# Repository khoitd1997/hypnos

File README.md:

# hypnos

Module embedded inside users' laptop to "remind" them to take break and sleep

## Background

I used to have a script that runs every couple hours to turn the computer off to remind me to take a break. However, that script can be easily bypassed and it's not cross-platform. Embedding `hypnos` into the motherboard of my laptop and enabling tamperproof protection in the BIOS for the case make it much harder to bypass.

## Features

- Interact with device through phone app
  - Allow users' actions to be asynchronous, save and transmit their actions when the device is connected
  - Allow a limited number of exceptions through tokens per month: Allow users to select a time range that they don't want to be disturbed, the number of tokens needed are automatically calculated and applied
    - Waving sleep time as well as applying many tokens in the same day should cost more to prevent binge
  - Customizable work and break duration(there has to be an upper and lower limit though)
  - Limit amount of total screen time per day
  - Statistics for tracking progress
  - Foreground task to show device status as well as current phase
  - Synchronize with app to keep correct time, remind users to connect to device if they haven't for a long time
  - Indicate the current time stretch
  - Bed time and wake time
  - Battery indicator
- Flexibly adapt to user' start of day
- Hard to abuse or bypass but also possible to remove when truly necessary
- Low power consumption
- User has pending actions like changing rest interval
- Need corrective actions such as clock syncing
- Reset switch for resetting all settings(including BLE bonding information)
- Small size: About 1.5 x 1.5 inch

## Custom GATT

The custom service is called the `Timetable Service`. `Base and other UUIDs` are taken [here](https://github.com/NordicPlayground/nRF5x-custom-ble-service-tutorial):

```c
// base is f364adc9-b000-4042-ba50-05ca45bf8abc
#define UUID_SERVICE 0x1400
```

To store an hour:minute info, needs 11 bits(5 for hour, 6(least significant) for minute) for 24-hour format. All timing is stored that way except for the current time service.

All times are in GMT.

All would require authentication to read/write

| UUID   | Type                  | Data Type              | Range                           |
| ------ | --------------------- | ---------------------- | ------------------------------- |
| 0x1401 | MORNING_CURFEW_END    | time type              | 24-hour format                  |
| 0x1402 | NIGHT_CURFEW_START    | time type              | 24-hour format                  |
| 0x1403 | WORK_DURATION_MINUTE  | uint8                  | 30-120                          |
| 0x1404 | BREAK_DURATION_MINUTE | uint8                  | 5-15                            |
| 0x1405 | ACTIVE_EXCEPTIONS     | list of pair unix time | 0-4 exceptions                  |
| 0x1406 | TOKENS_LEFT           | uint8                  | depend on policy implementation |
| 0x1407 | CURRENT_UNIX_TIME     | uint32                 | until saturation                |

Max of 4 exceptions can be active at one time

## References

[BLE Chips Power Consumption](https://www.argenox.com/library/bluetooth-low-energy/bluetooth-le-chipset-guide-2019/#ble-device-comparison)
[Picking Advertising Interval](https://www.beaconzone.co.uk/ibeaconadvertisinginterval)

[Current Time Service](https://stackoverflow.com/questions/35695711/how-to-correctly-set-the-date-and-time-in-a-bluetooth-low-energy-peripheral)

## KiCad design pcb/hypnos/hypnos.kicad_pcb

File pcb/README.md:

# PCB

## Constraints

Use the area of the spare network card. That area has nice cable management path from the side that has the off switch.

- Max Length: 32 mm inside flat area, 8 mm outside at the first 11 mm in width (not overlapping a lot of PCB just wires)
- Max Width: 30 mm inside flat area, 20 mm overlapping with MB PCB (Need 9.5 mm for BT840F)
- Max Height: 5 mm

[NRF52 Max Voltage for GPIO][1]

The antenna inside the T480s should be 50 ohm.

## BT840F PCB Layout Notes

2-sided PCB is sufficient.

## Notes

The bare right angle pin has height 2.5 mm

[1]: https://infocenter.nordicsemi.com/index.jsp?topic=%2Fcom.nordic.infocenter.nrf52832.ps.v1.1%2Fabs_max_ratings.html

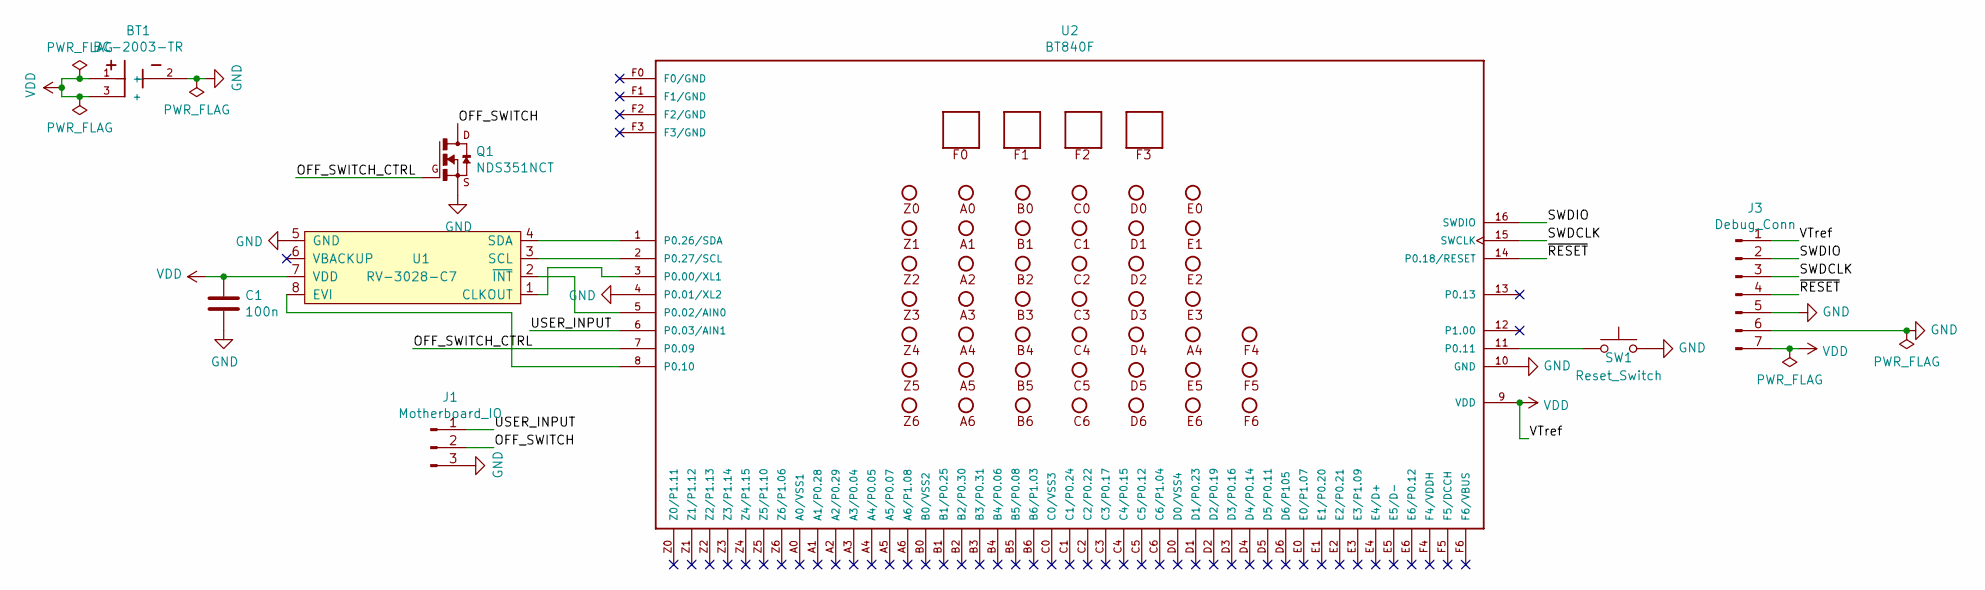
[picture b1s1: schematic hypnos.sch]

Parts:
BT1: BC-2003-TR
C1: 100n; C_0805_2012Metric_Pad1.15x1.40mm_HandSolder
J1: Motherboard_IO; Conn-Female-RightAnglex3-SMD
J3: Debug_Conn; Conn-Female-RightAnglex7-SMD
Q1: NDS351NCT; SOT-323_SC-70_Handsoldering
SW1: Reset_Switch; SW_KSR223GLFG
U1: RV-3028-C7
U2: BT840F

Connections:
/OFF_SWITCH: J1.2, Q1.3 (D)
/OFF_SWITCH_CTRL: Q1.1 (G), U2.7 (P0.09)
/SWDCLK: J3.3, U2.15 (SWCLK)
/SWDIO: J3.2, U2.16 (SWDIO)
/USER_INPUT: J1.1, U2.6 (P0.03/AIN1)
/~RESET: J3.4, U2.14 (P0.18/RESET)
GND: BT1.2 (-), C1.2, J1.3, J3.5, J3.6, Q1.2 (S), SW1.2, U1.5 (GND), U2.4 (P0.01/XL2), U2.10 (GND)
unnamed: SW1.1, U2.11 (P0.11)
unnamed: U1.1 (CLKOUT), U2.3 (P0.00/XL1)
unnamed: U1.2 (~INT), U2.5 (P0.02/AIN0)
unnamed: U1.3 (SCL), U2.2 (P0.27/SCL)
unnamed: U1.4 (SDA), U2.1 (P0.26/SDA)
unnamed: U1.8 (EVI), U2.8 (P0.10)
VDD: BT1.1 (+), BT1.3 (+), C1.1, J3.1, J3.7, U1.7 (VDD), U2.9 (VDD)

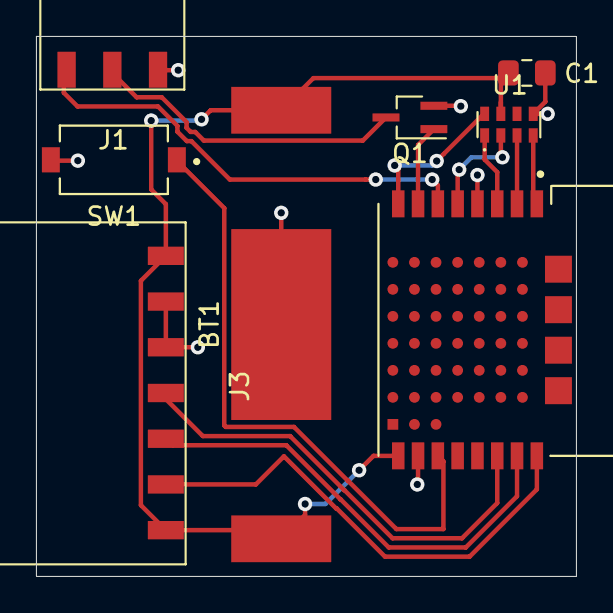
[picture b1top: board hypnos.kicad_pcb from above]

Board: 2 copper layers, 30.0 x 30.0 mm, 8 parts (0 on the bottom side), 14 nets.

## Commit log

2020-04-09 added basic file structure
2020-04-09 added background and features to README
2020-04-11 updated README with more details
2020-04-11 added oscilloscope current measurement guide
2020-04-11 added base nrf52 code
2020-04-11 switched nrf52840
2020-04-12 added firmware test plan
2020-04-12 removed unused reference
2020-04-12 added base app
2020-04-12 got app to work
2020-04-12 made foreground service start on startup and persistent
2020-04-12 have decent icon
2020-04-12 integrated shared preferences
2020-04-12 added foregroundServiceType
2020-04-13 integrated pca10059 into build system
2020-04-13 made pca10059 warning better
2020-04-13 refactored sdk_config to not duplicate
2020-04-13 fixed compile_commands.json path
2020-04-13 removed duplicate service starter
2020-04-14 handled inconsistent bond state
2020-04-14 added power consumption data
2020-04-14 bumped security level for gap
2020-04-14 handled repairing better
2020-04-14 added more feature notes
2020-04-16 Modified current measurement and add resources
2020-04-16 converted to cpp and semi-finalized advertising settings
2020-04-16 changed namespace indentation rule
2020-04-16 refactored advertising module
2020-04-16 replace memset with 0 initialization
2020-04-17 refactored bms, pm and qwr
2020-04-17 removed dis
2020-04-17 removed dis include
2020-04-17 moved delete bonds unsafe to correct place
2020-04-17 refactored power module
2020-04-17 refactored connection
2020-04-17 replaced pm macro with constexpr
2020-04-17 refactored ble stack module
2020-04-17 added ble namespace
2020-04-17 refactored gap
2020-04-17 refactored gatt
2020-04-17 refactored misc module
2020-04-17 Initial BLE firmware and App (#11)
2020-04-17 back up app
2020-04-17 added missing commit from last PR
2020-04-18 added custom gatt
2020-04-18 corrected information based on custom example
2020-04-18 Design custom gatt (#15)
2020-04-19 changed vscode script path to scripts
2020-04-19 configured vscode file association
2020-04-19 added batter service
2020-04-19 fixed vscode path variables
2020-04-19 made bas blocking
2020-04-19 moved battery calculation to adc
2020-04-19 enable low power mode
2020-04-19 disable battery timer
2020-04-19 added notes regarding which method to use for system off
2020-04-19 moved nrf52 links to firmware folder
2020-04-22 removed links
2020-04-22 fixed wrong adc read sequence
2020-04-22 added battery read for android
2020-04-22 addressed PR
2020-04-22 Battery service (#16)
2020-04-23 Added state machine link
2020-04-23 Added state machine (#22)
2020-04-24 used same linker script for both board
2020-04-24 revised the custom gatt
2020-04-24 added base timetable service
2020-04-24 gave custom type its own observer priority
2020-04-24 removed unused comments and typedef
2020-04-25 trim timetable service to minimum
2020-04-25 renamed stuffs
2020-04-27 added notes about tooling
2020-04-29 made toolchain board indepdendent
2020-04-29 added mtu, DLE, 2Mbps PHY
2020-04-30 bring global variable local
2020-05-01 moved build system to be more CMake dependent
2020-05-01 update program variable name
2020-05-01 added how to build docs
2020-05-01 fixed flash softdevice target
2020-05-01 added vscode stuffs
2020-05-01 added base exception list characteristic
2020-05-02 added base unit test structure
2020-05-02 added documentation about building test
2020-05-02 fixed typos
2020-05-02 add vscode stuffs
2020-05-02 added time exception list unit tests
2020-05-02 bumped ble stack size
2020-05-06 replaced ble library
2020-05-06 removed polidea mention
2020-05-06 fixed wrong base uuid
2020-05-06 templatized timetable service
2020-05-07 switched epoch to uint32_t
2020-05-07 added time exception for app side
2020-05-08 added uuid for the rest of characteristic
2020-05-08 refactored and fixed a bug in characteristic read
2020-05-09 added system view files
2020-05-09 added some systemview stuffs
2020-05-09 refactored service to expose characteristic
2020-05-10 ble gatt bidirectionally working
2020-05-10 added ipc command for timetable
2020-05-10 Implement custom gatt (#26)
2020-05-10 added base twi
2020-05-10 moved twi to its own module
2020-05-10 added rtc3028 driver
2020-05-10 tested RTC
2020-05-11 added timezone stuffs
2020-05-11 deleted test code
2020-05-11 added gpio I/O and interrupt
2020-05-11 tested rv3028 interrupt capability
2020-05-11 Rv3028 and GPIO driver (#28)
2020-05-11 rename epoch to unix for consistency
2020-05-11 added characteristic for both side
2020-05-11 moved updating characteristic to be closer to when it's actually read
2020-05-11 Current unix time characteristic (#29)
2020-05-20 added flag to enable assert
2020-05-20 added delay for rv3028 in accordance with spec sheet
2020-05-20 added default arg for eeprom read/write
2020-05-20 disable UART log
2020-05-20 use macros for time unit
2020-05-20 added storage manager
2020-05-20 fixed wrong rtc ref
2020-05-20 flush logs in assert cb
2020-05-21 added timed sleep
2020-05-24 Persistent storage (#31)
2020-05-24 added timestamp
2020-05-24 move test EEPROM to correct file
2020-05-24 added isInBreak and sleep
2020-05-24 added debug and release config
2020-05-24 added notes about sleep
2020-05-24 Sleep mode (#32)
2020-05-25 added base plantuml file
2020-05-30 adjust shutdown and start work behavior
2020-05-30 updated state diagram pic
2020-05-30 Plantuml (#34)
2020-05-31 added computer switch module
2020-05-31 added computer switch module (#35)
2020-05-31 added bonded check
2020-05-31 added wakeup reason check
2020-06-01 added state machine
2020-06-01 separated enable and set for alarm
2020-06-01 use gpiote instead of gpio for wakeup
2020-06-01 fixed issue during PR
2020-06-01 changed connection handle access
2020-06-01 Implent state machine (#36)
2020-06-01 added initial pcb
2020-06-03 finished schematics, ready for pcb
2020-06-07 changed pin assignments
2020-07-07 backup work
